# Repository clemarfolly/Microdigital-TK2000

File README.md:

# Microdigital - TK2000

A Microdigital Eletrônica Ltda foi uma das empresas pioneiras no mercado de microcomputadores no Brasil, tendo grande importância na popularização da informática durante a década de 1980. Fundada em 1979, a empresa se destacou por criar e distribuir uma série de microcomputadores compatíveis com modelos internacionais. A Microdigital se beneficiou da reserva de mercado imposta pelo governo brasileiro, o que levou a empresa a desenvolver produtos que atendessem à demanda interna por tecnologia, educação e entretenimento.

Entre os produtos está o TK2000, lançado oficialmente em 1984 após ser apresentado na Feira de Informática de 1983. Inspirado no Apple II, o TK2000 foi um microcomputador voltado para o mercado doméstico e educacional, parcialmente compatível com o software do Apple II, mas com algumas limitações em termos de hardware, o que o tornava mais acessível ao consumidor brasileiro. Equipado com uma CPU 6502, 16k de ROM e 64k de RAM, o TK2000 era, na verdade, um clone do Micro-Professor MPF-II, um modelo taiwanês fabricado pela Multitech (futura Acer). O sucesso do TK2000 consolidou a Microdigital como uma das líderes no mercado de microcomputadores no Brasil, contribuindo significativamente para a difusão da cultura computacional no país durante os anos 80. Em 1985, foi lançada uma versão aprimorada, o TK2000 II, que incluía uma opção de 128K de memória. O microcomputador foi descontinuado em 1987.

## Sobre essa reprodução

A reprodução do projeto foi realizada sem acesso físico à placa original, com base em fotos encontradas na internet. Para isso, utilizou-se os software Sprint Layout e o KiCad para desenhar o esquema e a placa de circuito impresso. A réplica ainda não foi produzida, e seu funcionamento não foi validado. Agradecemos às pessoas que disponibilizaram as fotos e o esquema original, permitindo que esse trabalho fosse possível.

 ### Datalhes da placa
A placa é dupla face e o tamanho final ficou com 237x170 mm.

### Comparação com a placa original
Embora eu não tenha tido acesso direto à placa original, me esforcei para que a recriação fosse a mais fiel possível. Algumas imagens de referência estavam em baixa resolução e precisaram ter suas proporções ajustadas, além de estarem com componentes e adesivos, o que dificultou a reprodução das trilhas que passavam por baixo deles.

A parte de RF foi removida e no lugar colocada uma saída de áudio. Além disso, o jumper que conecta o pino 28 da ROM U39 ao pino 7 do 74LS244 foi integrado diretamente ao roteamento da placa, permetindo o uso de uma ROM 27C128.

### Para confecção

Na seção de releases desta página, você encontrará todos os arquivos necessários para a fabricação da placa: o gerber em formato zip, o esquema em PDF e a lista interativa de materiais em HTML. Basta enviar o arquivo zip para a sua fabricante de PCB de preferência.

### Chip customizado

A montagem requer a gravação de um chip PLD GAL16V8, o conteúdo está na pasta PAL. Mais detalhes em: 

https://www.facebook.com/groups/cidadedosclassicos/posts/5769043533153302/?paipv=0&eav=AfbpHolPJ6P4nDAmXXkvS--qkC2yUR-xJ5SVl_j7wmNv-nLbxHa_C_v81FATnQMoCv0&_rdr

## Créditos

### Recriação da Placa: 

Clemar Folly Jr.

https://x.com/clemarfolly/ - https://www.facebook.com/clemarjr

### Fotos

Clube do TK90X

http://www.tk90x.com.br/Projetos_TK2000_clareamento.html

José Ferro - Recebido via E-mail

Tabajara Labs

http://tabalabs.com.br/tk2k/reparo_teclado/

Grupo Microdigital TK 2000 no Facebook

https://www.facebook.com/groups/2839171526116039/

Uma saída de som para o TK2000

https://www.victortrucco.com/TK/TK2000Som/TK2000Som

### Esquema

TK2000 - Esquema Elétrico Placa Principal - Datassette

https://datassette.org/manuais/hardware-tk-2000-microdigital-eletronica-manuais/tk2000-esquema-eletrico-placa-principal

#### Caso queira contribuir para que outras reproduções como esta sejam feitas, considere fazer uma doação.

Chave pix: clemarjr@gmail.com

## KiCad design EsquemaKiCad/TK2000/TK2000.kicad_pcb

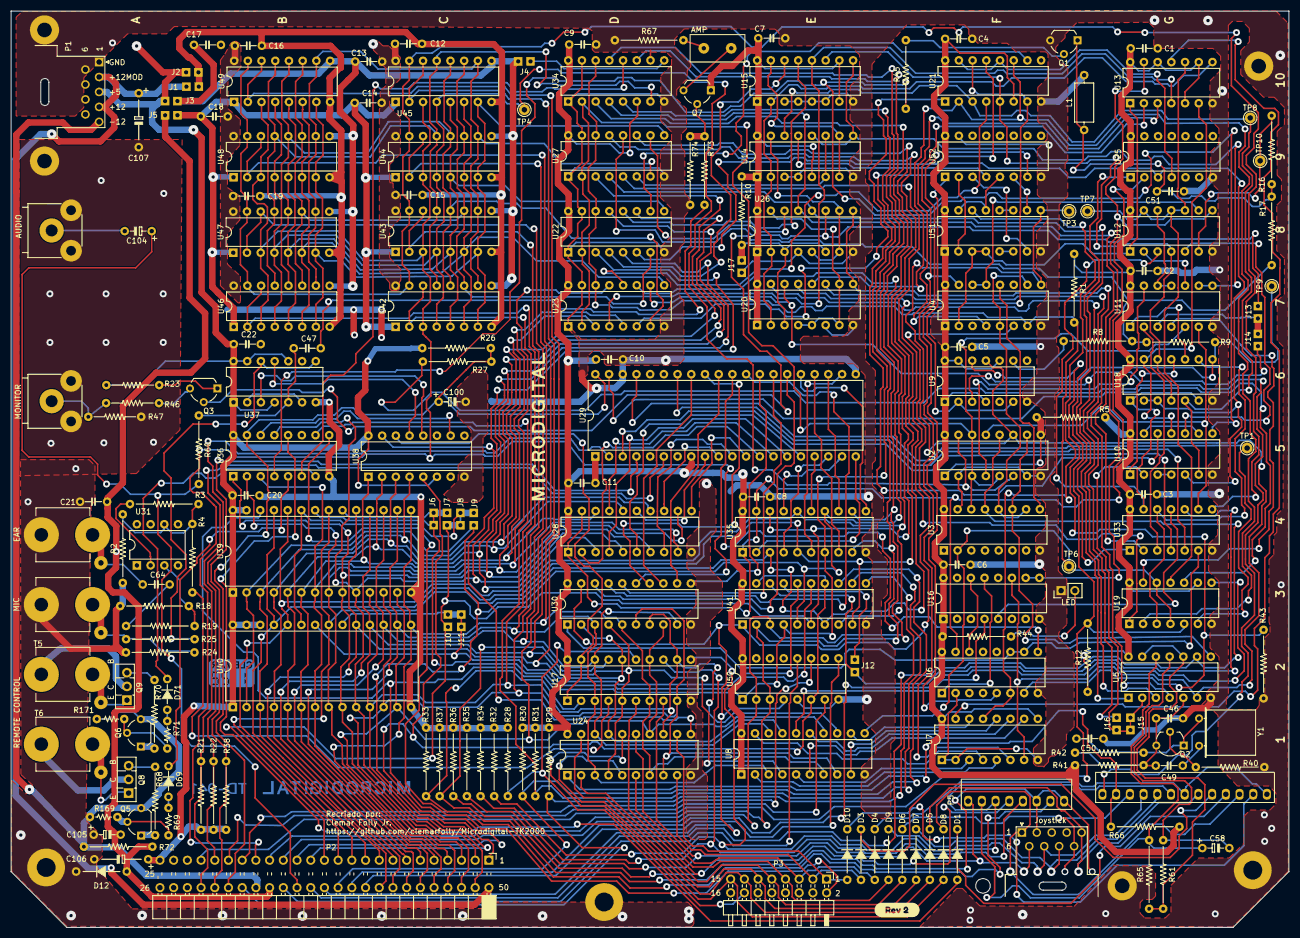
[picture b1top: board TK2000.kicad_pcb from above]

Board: 2 copper layers, 236.8 x 169.8 mm, 206 parts (0 on the bottom side), 255 nets.

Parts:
C1, C2, C3, C4, C5, C6, C7, C8, C9, C10, C11, C12, C13, C14, C15, C16, C17, C18, C19, C20, C21, C22: 0.1; C_Disc_D4.3mm_W1.9mm_P5.00mm
C46, C47, C49, C50, C51: C_Small; C_Disc_D4.3mm_W1.9mm_P5.00mm
C58, C100: C_Polarized_Small; C_Polarized_P5.00mm
C64: ?; C_Disc_D4.3mm_W1.9mm_P5.00mm
C104: 1uF; C_Polarized_P5.00mm
C105: 47uF; C_Polarized_P5.00mm
C106, C107: 100uF; C_Polarized_P10.00mm
D1, D3, D4, D5, D6, D7, D8, D9, D10: D_Small; Diodo_9.38mm
D12: 5V1; Diodo_9.38mm
D13: LED; PinHeader_1x02_P2.54mm_Vertical
D69, D71: 1N4148; Diodo_5.715mm
H1, H2, H3: MountingHole_Pad; MountingHole_3.5mm_Pad
H4, H6, H7, H8: MountingHole_Pad; MountingHole_2.7mm_Pad
H5: MountingHole_Pad; MountingHole_2.7mm
J1, J3, J4, J5, J7, J9, J10, J14, J16: SolderJumper_2_Open; Jumper_Open
J2: TK2000:Jumper_Open; Jumper_Open
J6, J8, J11, J12: SolderJumper_2_Open; Jumper_Bridged
J13, J15: Jumper_Bridged
J17: SolderJumper_2_Open_Small; Jumper_Open
J100: Joystick; DSUB-9_Male_Horizontal_P2.77x2.54mm_EdgePinOffset9.40mm
L1: 47uH; L_Axial_L7.0mm_D3.3mm_P10.16mm_Horizontal_Fastron_MICC
LS1: AMP; Connector_AMP
P1: POWER; DSUB-9_Male_Horizontal_P2.77x2.54mm_EdgePinOffset9.40mm
P2: Conector de Expansão; PinSocket_2x25_P2.54mm_Horizontal
P3: P3; PinHeader_2x08_P2.54mm_Horizontal
P5: Conector_P5; Connector_P5
Q1, Q3, Q5, Q6, Q7: BC548; TO-92_Wide
Q2: BF494B; TO-92_Wide_Invert
Q8, Q9: BD140; TO-126-3_Vertical
R1, R2, R5, R10, R12, R16, R21, R22, R26, R28, R29, R30, R31, R32, R33, R34, R35, R36, R37, R38, R43, R45, R61, R65, R66: 1k; Resistor_P12.7mm_Horizontal
R3: 1M; Resistor_P12.7mm_Horizontal
R4, R9, R18, R19, R25: 12k; Resistor_P12.7mm_Horizontal
R8, R27: 1k5; Resistor_P12.7mm_Horizontal
R17: 2k; Resistor_P12.7mm_Horizontal
R23, R46, R47: 1k; Resistor_P9.8mm_Horizontal
R24: 100; Resistor_P12.7mm_Horizontal
R40, R41, R42: 47; Resistor_P12.7mm_Horizontal
R44: 220; Resistor_P12.7mm_Horizontal
R60: 560; Resistor_P12.7mm_Horizontal
R67, R72, R73, R74: ?; Resistor_P12.7mm_Horizontal
R68, R70: 470; Resistor_P12.7mm_Horizontal
R69, R71: 5k6; Resistor_P5.08mm_Vertical
R169, R171: 3k3; Resistor_P5.08mm_Vertical
T2: MONITOR; RCA_AV-8,4-5A
T3: EAR; J2_Mono_Panel
T4: MIC; J2_Mono_Panel
T5: B - Remote; J2_Mono_Panel
T6: A - Remote; J2_Mono_Panel
T7: AUDIO; RCA_AV-8,4-5A
TP1, TP3, TP6, TP7, TP8, TP9, TP10: TestPoint_Small; Pin_D1.0mm_L10.0mm
TP4: ~{CAS}; Pin_D1.0mm_L10.0mm
U2, U16: 74LS194; DIP-16_W7.62mm
U3, U22, U23, U27, U34: 74LS153; DIP-16_W7.62mm
U4: 74LS175; DIP-16_W7.62mm
U5, U25: 74LS04; DIP-14_W7.62mm
U6: 74LS253; DIP-16_W7.62mm
U7: 74LS166; DIP-16_W7.62mm
U8, U24: 74LS273; DIP-20_W7.62mm
U9, U37: 74LS74; DIP-14_W7.62mm
U10, U11: 74LS02; DIP-14_W7.62mm
U12: 74LS11; DIP-14_W7.62mm
U13: 74LS86; DIP-14_W7.62mm
U14, U15, U20, U26: 74LS161; DIP-16_W7.62mm
U17, U28, U35: 74LS244; DIP-20_W7.62mm
U18: 74LS51; DIP-14_W7.62mm
U19: 74LS08; DIP-14_W7.62mm
U21: 74LS283; DIP-16_W7.62mm
U29: 6502; DIP-40_W15.24mm
U30: 74LS245; DIP-20_W7.62mm
U31: LM741; DIP-8_W7.62mm
U33: 74LS32; DIP-14_W7.62mm
U36: 74LS259; DIP-16_W7.62mm
U38, U50: 74LS138; DIP-16_W7.62mm
U39, U40: 2764; DIP-28_W15.24mm
U41: PAL14L4; DIP-20_W7.62mm
U42: 4116_U42; DIP-16_W7.62mm
U43: 4116_U43; DIP-16_W7.62mm
U44, U45, U46, U47: 4116_U47; DIP-16_W7.62mm
U48, U49: 4116; DIP-16_W7.62mm
U51: 74LS174; DIP-16_W7.62mm
U52: 74LS157; DIP-16_W7.62mm
Y1: Crystal; Crystal_HC52-U_Horizontal
kibuzzard-6AD42836: G***; kibuzzard-6AD42836

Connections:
+5V: C1.1, C2.1, C3.1, C4.1, C5.1, C6.1, C7.1, C8.1, C9.1, C10.1, C11.1, C20.1, C22.1, C106.1, J2.2 (B), J3.2 (B), P1.3, P2.25, Q7.1 (C), R1.1, R5.2, R10.1, R12.1, R21.1, R22.1, R23.2, R26.1, R29.1, R30.1, R31.1, R38.1, R41.1, R44.2, R66.1, U2.16 (VCC), U3.16 (VCC), U4.1 (~Mr), U4.16 (VCC), U5.14 (VCC), U6.16 (VCC), U7.9 (~Clr), U7.16 (VCC), U8.1 (~MR), U8.20 (VCC), U9.1 (CL1), U9.4 (PR1), U9.10 (PR2), U9.13 (CL2), U9.14 (VCC), U10.14 (VCC), U11.14 (VCC), U12.14 (VCC), U13.5, U13.9, U13.12, U13.14 (VCC), U14.1 (~MR), U14.5 (D2), U14.16 (VCC), U15.1 (~MR), U15.7 (CEP), U15.10 (CET), U15.16 (VCC), U16.1 (Mr), U16.16 (VCC), U17.20 (VCC), U18.14 (VCC), U19.9, U19.14 (VCC), U20.1 (~MR), U20.16 (VCC), U21.6 (B1), U21.16 (VCC), U22.16 (VCC), U23.16 (VCC), U24.20 (VCC), U25.14 (VCC), U26.1 (~MR), U26.16 (VCC), U27.16 (VCC), U28.20 (VCC), U29.8 (VCC), U30.20 (VCC), U31.7 (V+), U33.14 (VCC), U34.6 (I0a), U34.16 (VCC), U35.20 (VCC), U36.16 (VCC), U37.1 (CL1), U37.4 (PR1), U37.10 (PR2), U37.13 (CL2), U37.14 (VCC), U38.6 (G1), U38.16 (VDD), U39.1 (VPP), U39.27 (~PGM), U39.28 (VCC), U40.1 (VPP), U40.26 (NC), U40.27 (~PGM), U40.28 (VCC), U41.20 (VCC), U50.16 (VDD), U51.1 (~Mr), U51.16 (VCC), U52.16 (VCC)
+12V: C107.1, J1.2 (B), P1.2, P1.4, P2.50
-5V: C21.1, C105.2, D12.2 (A), J5.2 (B), P2.34, R72.1, U31.4 (V-)
-12V: P1.5, P2.33, Q5.3 (E), Q6.3 (E), R72.2, R169.1, R171.2
GND: C1.2, C2.2, C3.2, C4.2, C5.2, C6.2, C7.2, C8.2, C9.2, C10.2, C11.2, C12.2, C13.2, C14.2, C15.2, C16.2, C17.2, C18.2, C19.2, C20.2, C21.2, C22.2, C46.2, C50.1, C51.2, C100.2, C105.1, C106.2, C107.2, D12.1 (K), D13.1 (K), H1.1, H2.1, H3.1, H4.1, H6.1, H7.1, H8.1, J17.1 (A), L1.2, P1.1, P1.6, P1.7, P1.8, P1.9, P2.26, P3.4, P3.6, P3.8, P3.10, P3.12, Q1.3 (E), R2.1, R18.1, R24.1, R28.1, R32.1, R33.1, R34.1, R35.1, R36.1, R37.1, R40.1, R43.2, R47.1, R67.1, R74.1, T2.2 (Ext), T3.2 (Ext), T4.2 (Ext), T7.2 (Ext), U2.2 (Dsr), U2.7 (Dsl), U2.8 (GND), U3.8 (GND), U3.15 (~Eb), U4.8 (GND), U5.7 (GND), U6.2 (A1), U6.8 (GND), U7.1 (Ds), U7.2 (D0), U7.8 (GND), U8.10 (GND), U9.7 (GND), U10.7 (GND), U11.7 (GND), U12.7 (GND), U13.7 (GND), U14.3 (D0), U14.4 (D1), U14.8 (GND), U15.3 (D0), U15.4 (D1), U15.5 (D2), U15.6 (D3), U15.8 (GND), U16.8 (GND), U17.10 (GND), U18.7 (GND), U19.7 (GND), U20.6 (D3), U20.8 (GND), U21.8 (GND), U22.1 (~Ea), U22.8 (GND), U22.15 (~Eb), U23.1 (~Ea), U23.8 (GND), U23.15 (~Eb), U24.10 (GND), U25.7 (GND), U26.4 (D1), U26.8 (GND), U27.1 (~Ea), U27.8 (GND), U27.15 (~Eb), U28.10 (GND), U29.1 (VSS), U29.21 (VSS), U29.38 (SO), U30.10 (GND), U33.7 (GND), U34.1 (~Ea), U34.8 (GND), U34.10 (I0b), U34.15 (~Eb), U35.10 (GND), U36.8 (GND), U37.7 (GND), U38.8 (VSS), U39.14 (GND), U40.14 (GND), U41.10 (VSS), U42.16 (GND), U43.16, U44.16, U45.16, U46.16, U47.16, U48.16, U49.16, U50.5 (~G2B), U50.8 (VSS), U51.8 (GND), U52.8 (GND), U52.15 (~E)
J3_P1: C13.1, C17.1, J3.1 (A), J4.1 (A), U42.9, U43.9, U44.9, U45.9, U46.9, U47.9, U48.9, U49.9
unnamed: C47.2, R73.1
unnamed: C49.1, Y1.1
unnamed: C58.1, P5.2, R65.2, U5.12
unnamed: C58.2, R61.1, U5.11
unnamed: C64.2, R19.2
unnamed: D1.2 (A), U36.12 (Q7)
unnamed: D1.1 (K), P5.18
unnamed: D3.2 (A), P3.3, U24.9 (4Q)
unnamed: D3.1 (K), P5.17
unnamed: D4.2 (A), P3.5, U24.15 (6Q)
unnamed: D4.1 (K), P5.15, P5.21
unnamed: D5.2 (A), P3.13, U24.5 (2Q)
unnamed: D5.1 (K), J100.5, P5.16
unnamed: D6.2 (A), P3.9, U24.2 (1Q)
unnamed: D6.1 (K), J100.9, P5.11
unnamed: D7.2 (A), P3.11, U24.19 (8Q)
unnamed: D7.1 (K), J100.8, P5.13
unnamed: D8.2 (A), P3.15, U24.16 (7Q)
unnamed: D8.1 (K), J100.1, P5.19
unnamed: D9.2 (A), P3.7, U24.6 (3Q)
unnamed: D9.1 (K), J100.7, P5.12
unnamed: D10.2 (A), P3.1, U24.12 (5Q)
unnamed: D10.1 (K), P5.20
unnamed: D13.2 (A), R44.1
unnamed: D69.2 (A), R69.1
unnamed: D69.1 (K), U36.5 (Q1)
unnamed: D71.2 (A), R71.1
unnamed: D71.1 (K), U36.7 (Q3)
unnamed: J4.2 (B), U34.9 (Zb)
unnamed: J6.1 (A), J6.2 (B), J7.1 (A), U39.20 (~CE), U39.22 (~OE), U41.15
unnamed: J10.1 (A), J11.1 (A), J11.2 (B), U40.20 (~CE), U40.22 (~OE), U41.16
unnamed: J12.1 (A), U41.17
unnamed: J12.2 (B), U33.10, U41.18
unnamed: J13.1 (A), J14.2 (B), U11.3
unnamed: J13.2 (B), U26.11 (Q3), U27.12 (I2b)
unnamed: J14.1 (A), U5.1, U20.14 (Q0), U23.10 (I0b)
unnamed: J15.1 (A), J15.2 (B), J16.2 (B), U5.2, U10.2
unnamed: J16.1 (A), U20.11 (Q3)
unnamed: J17.2 (B), R10.2, U20.3 (D0), U26.3 (D0), U26.6 (D3)
unnamed: LS1.2, R67.2
unnamed: P5.22, R27.2
unnamed: Q1.2 (B), R45.2
unnamed: C51.1, L1.1, Q1.1 (C), R16.2, R17.1
unnamed: C50.2, Q2.1 (B), R42.2, Y1.2
unnamed: C46.1, C49.2, Q2.3 (C), R41.2, R42.1, U5.5
unnamed: Q2.2 (E), R40.2
unnamed: Q3.2 (B), R8.2, R9.2, R17.2
unnamed: Q3.1 (C), R23.1
unnamed: Q3.3 (E), R46.2
unnamed: Q5.2 (B), R69.2, R169.2
unnamed: Q5.1 (C), R68.2
unnamed: Q6.2 (B), R71.2, R171.1
unnamed: Q6.1 (C), R70.1
unnamed: Q7.2 (B), R73.2, R74.2
unnamed: LS1.1, Q7.3 (E)
unnamed: Q8.3 (B), R68.1
unnamed: Q8.2 (C), T6.2 (Ext)
unnamed: Q8.1 (E), T6.1 (In)
unnamed: Q9.3 (B), R70.2
unnamed: Q9.2 (C), T5.2 (Ext)
unnamed: Q9.1 (E), T5.1 (In)
unnamed: R2.2, R3.2, R4.1, U31.6
unnamed: R16.1, TP10.1, U12.6
unnamed: R61.2, R65.1, U5.10, U5.13
unnamed: R46.1, R47.2, T2.1 (In)
unnamed: C64.1, T3.1 (In)
unnamed: R24.2, R25.2, T4.1 (In)
unnamed: C104.2, T7.1 (In)
unnamed: TP7.1, U12.10, U12.11, U12.13, U13.10, U19.11
unnamed: R5.1, U2.1 (Mr), U2.9 (S0)
unnamed: U2.3 (P0), U2.5 (P2), U2.14 (Q1), U3.14 (S0), U11.5, U22.2 (S1), U23.2 (S1), U27.2 (S1), U34.2 (S1)
unnamed: U2.4 (P1), U11.13
unnamed: TP4.1, U2.6 (P3), U2.15 (Q0), U42.4, U43.4, U44.4, U45.4, U46.4, U47.4, U48.4, U49.4
unnamed: U2.13 (Q2), U11.6, U33.9
unnamed: U2.10 (S1), U3.11 (I1b), U5.8
unnamed: U3.10 (I0b), U3.12 (I2b), U4.5 (D1), U4.10 (Q2)
unnamed: U3.9 (Zb), U4.12 (D2)
unnamed: U4.4 (D0), U13.3
unnamed: U4.13 (D3), U4.14 (~Q3), U12.9
unnamed: U4.2 (Q0), U12.1, U13.1, U51.3 (D0), U51.4 (D1)
unnamed: U4.15 (Q3), U7.6 (CE), U13.2
unnamed: R43.1, U6.7 (Za), U9.12 (D2)
unnamed: U7.3 (D1), U8.5 (2Q)
unnamed: U7.4 (D2), U8.19 (8Q)
unnamed: U7.5 (D3), U8.2 (1Q)
unnamed: U7.10 (D4), U8.6 (3Q)
unnamed: U7.11 (D5), U8.15 (6Q)
unnamed: U7.12 (D6), U8.9 (4Q)
unnamed: U7.14 (D7), U8.12 (5Q)
unnamed: U7.15 (PE), U13.11
unnamed: R9.1, TP9.1, U9.3 (CK1), U18.8
unnamed: R8.1, U9.9 (Q2)
unnamed: U10.1, U18.11
unnamed: U10.3, U10.4
unnamed: U10.10, U12.5
unnamed: U10.11, U13.6, U18.13
unnamed: U10.9, U10.13
unnamed: U11.1, U18.10
unnamed: U11.2, U33.3
unnamed: U11.4, U19.13
unnamed: U11.10, U12.2
unnamed: U11.11, U11.12, U12.12
unnamed: U12.3, U18.1, U18.6, U33.13
unnamed: U14.7 (CEP), U14.10 (CET), U15.15 (TC)
unnamed: U13.8, U14.2 (CP), U15.2 (CP), U20.2 (CP), U26.2 (CP)
unnamed: U14.6 (D3), U14.11 (Q3), U27.6 (I0a)
unnamed: TP8.1, U10.6, U14.14 (Q0), U18.5, U21.3 (A2)
unnamed: U10.5, U14.13 (Q1), U18.2, U18.3, U25.3
unnamed: U11.8, U11.9, U14.9 (~PE), U14.12 (Q2), U15.9 (~PE)
unnamed: U14.15 (TC), U26.5 (D2), U26.7 (CEP), U26.10 (CET)
unnamed: U15.14 (Q0), U22.4 (I2a)
unnamed: U15.13 (Q1), U22.12 (I2b)
unnamed: U13.4, U15.12 (Q2), U23.4 (I2a)
unnamed: U12.4, U15.11 (Q3), U18.4, U18.12, U21.5 (A1)
unnamed: TP3.1, U2.11 (Cp), U4.9 (Cp), U5.6, U7.7 (Clk), U9.11 (CK2), U16.11 (Cp), U51.9 (Cp)
unnamed: U8.16 (7Q), U16.4 (P1)
unnamed: U16.5 (P2), U33.11
unnamed: U6.14 (A0), U16.14 (Q1)
unnamed: U6.1 (~OEa), U16.13 (Q2)
unnamed: U12.8, U13.13, U16.9 (S0), U16.10 (S1)
unnamed: P5.7, R33.2, U17.2 (I0a)
unnamed: P5.3, P5.14, R32.2, U17.11 (I0b)
unnamed: R4.2, U17.4 (I1a)
unnamed: P5.5, R34.2, U17.13 (I1b)
unnamed: P5.4, R36.2, U17.6 (I2a)
unnamed: P3.14, R28.2, U17.15 (I2b)
unnamed: J100.6, P5.1, R35.2, U17.8 (I3a)
unnamed: J100.2, P5.6, P5.8, R37.2, U17.17 (I3b)
unnamed: U17.1 (~OEa), U17.19 (~OEb), U38.14 (Y1)
unnamed: U18.9, U19.3, U33.12
unnamed: U20.4 (D1), U20.5 (D2), U20.7 (CEP), U20.10 (CET), U26.15 (TC)
unnamed: U19.1, U20.13 (Q1), U21.7 (C0), U21.14 (A3)
unnamed: U19.2, U20.12 (Q2), U21.2 (B2), U21.11 (B4)
unnamed: U5.3, U20.15 (TC)
unnamed: U5.4, U20.9 (~PE), U26.9 (~PE)
unnamed: U21.12 (A4), U21.15 (B3), U25.4
unnamed: U21.4 (S1), U23.12 (I2b)
unnamed: U21.1 (S2), U23.6 (I0a)
unnamed: U21.13 (S3), U22.6 (I0a)
unnamed: U21.10 (S4), U22.10 (I0b)
unnamed: R1.2, TP6.1, U3.2 (S1), U4.7 (Q1), U8.11 (CP), U19.4, U19.12, U22.14 (S0), U23.14 (S0), U27.14 (S0), U34.14 (S0)
unnamed: U22.7 (Za), U42.11, U43.11, U44.11, U45.11, U46.11, U47.11, U48.11, U49.11
unnamed: U22.9 (Zb), U42.5, U43.5, U44.5, U45.5, U46.5, U47.5, U48.5, U49.5
unnamed: U23.7 (Za), U42.12, U43.12, U44.12, U45.12, U46.12, U47.12, U48.12, U49.12
unnamed: U23.9 (Zb), U42.6, U43.6, U44.6, U45.6, U46.6, U47.6, U48.6, U49.6
unnamed: U24.11 (CP), U38.15 (Y0)
unnamed: P5.10, R66.2, U24.1 (~MR)
unnamed: U26.14 (Q0), U27.10 (I0b)
unnamed: U26.13 (Q1), U33.2, U34.4 (I2a)
unnamed: U26.12 (Q2), U27.4 (I2a), U33.1
unnamed: U27.7 (Za), U42.10, U43.10, U44.10, U45.10, U46.10, U47.10, U48.10, U49.10
unnamed: U27.9 (Zb), U42.7, U43.7, U44.7, U45.7, U46.7, U47.7, U48.7, U49.7
unnamed: U28.2 (I0a), U29.13 (AB4)
unnamed: U28.11 (I0b), U29.12 (AB3)
unnamed: U28.4 (I1a), U29.15 (AB6)
unnamed: U28.13 (I1b), U29.10 (AB1)
unnamed: U28.6 (I2a), U29.16 (AB7)
unnamed: U28.15 (I2b), U29.9 (AB0)
unnamed: U28.8 (I3a), U29.11 (AB2)
unnamed: U28.17 (I3b), U29.14 (AB5)
unnamed: U6.15 (~OEb), U25.2, U28.1 (~OEa), U28.19 (~OEb), U35.1 (~OEa), U35.19 (~OEb)
unnamed: U29.17 (AB8), U35.15 (I2b)
unnamed: U29.18 (AB9), U35.4 (I1a)
unnamed: U29.19 (AB10), U35.17 (I3b)
unnamed: U29.20 (AB11), U35.2 (I0a)
unnamed: U29.22 (AB12), U35.6 (I2a)
unnamed: U29.23 (AB13), U35.13 (I1b)
unnamed: U29.24 (AB14), U35.8 (I3a)
unnamed: U29.25 (AB15), U35.11 (I0b)
unnamed: U29.33 (DB0), U30.13 (B6)
unnamed: U29.32 (DB1), U30.14 (B5)
unnamed: U29.31 (DB2), U30.12 (B7)
unnamed: U29.30 (DB3), U30.15 (B4)
unnamed: U29.29 (DB4), U30.17 (B2)
unnamed: U29.28 (DB5), U30.11 (B8)
unnamed: U29.27 (DB6), U30.16 (B3)
unnamed: U29.26 (DB7), U30.18 (B1)
unnamed: TP1.1, U19.6, U29.37 (PHI0)
unnamed: U29.3 (PHI1), U33.4
unnamed: U19.10, U29.39 (PHI2)
unnamed: U29.34 (R/~W), U33.5
unnamed: U6.10 (I0b), U6.11 (I1b), U30.1 (DIR), U33.6
unnamed: R18.2, R19.1, U31.3 (+)
unnamed: R3.1, U31.2 (-)
unnamed: U34.12 (I2b), U36.6 (Q2)
unnamed: U34.7 (Za), U42.13, U43.13, U44.13, U45.13, U46.13, U47.13, U48.13, U49.13
unnamed: R45.1, U10.8, U36.4 (Q0)
unnamed: P3.2, U36.9 (Q4)
unnamed: R31.2, U36.10 (Q5), U41.12
unnamed: U36.14 (~E), U38.10 (Y5)
unnamed: U37.3 (CK1), U38.12 (Y3)
unnamed: U37.11 (CK2), U38.13 (Y2)
unnamed: U37.2 (D1), U37.6 (~Q1)
unnamed: R25.1, U37.8 (~Q2), U37.12 (D2)
unnamed: C47.1, R60.1, U37.5 (Q1)
unnamed: U33.8, U42.15, U43.15, U44.15, U45.15, U46.15, U47.15, U48.15, U49.15
unnamed: U51.5 (Q1), U51.6 (D2)
unnamed: U51.11 (D3), U51.12 (Q4)
unnamed: U51.13 (D4), U51.15 (Q5), U52.5 (I0b)
unnamed: U6.6 (I0a), U7.13 (Qh), U51.14 (D5)
unnamed: U51.2 (Q0), U52.2 (I0a)
unnamed: U51.7 (Q2), U52.3 (I1a)
unnamed: U51.10 (Q3), U52.6 (I1b)
unnamed: U9.2 (D1), U9.6 (~Q1), U52.1 (S)
unnamed: U10.12, U52.4 (Za)
unnamed: U6.5 (I1a), U52.7 (Zb)
P2_2M: P2.37, U2.12 (Q3), U3.13 (I3b), U5.9
P2_A0: P2.2, U22.3 (I3a), U28.5 (O2b), U36.13 (D), U39.10 (A0), U40.10 (A0)
P2_A1: P2.3, U22.13 (I3b), U28.7 (O1b), U36.1 (A0), U39.9 (A1), U40.9 (A1)
P2_A2: P2.4, U23.3 (I3a), U28.12 (O3a), U36.2 (A1), U39.8 (A2), U40.8 (A2)
P2_A3: P2.5, U23.13 (I3b), U28.9 (O0b), U36.3 (A2), U39.7 (A3), U40.7 (A3)
P2_A4: P2.6, U23.5 (I1a), U28.18 (O0a), U38.1 (A), U39.6 (A4), U40.6 (A4)
P2_A5: P2.7, U22.5 (I1a), U28.3 (O3b), U38.2 (B), U39.5 (A5), U40.5 (A5)
P2_A6: P2.8, U22.11 (I1b), U28.16 (O1a), U38.3 (C), U39.4 (A6), U40.4 (A6)
P2_A7: P2.9, U27.3 (I3a), U28.14 (O2a), U38.4 (~G2A), U39.3 (A7), U40.3 (A7)
P2_A8: P2.10, U27.13 (I3b), U35.5 (O2b), U39.25 (A8), U40.25 (A8), U41.9
P2_A9: P2.11, U23.11 (I1b), U35.16 (O1a), U39.24 (A9), U40.24 (A9), U41.8
P2_A10: P2.12, U27.5 (I1a), U35.3 (O3b), U39.21 (A10), U40.21 (A10), U41.7
P2_A11: J7.2 (B), J8.1 (A), J8.2 (B), J9.2 (B), J10.2 (B), P2.13, U27.11 (I1b), U35.18 (O0a), U39.23 (A11), U40.23 (A11), U41.6
P2_A12: J9.1 (A), P2.14, U34.3 (I3a), U35.14 (O2a), U39.2 (A12), U40.2 (A12), U41.5
P2_A13: P2.15, U34.5 (I1a), U35.7 (O1b), U39.26 (A13), U41.4, U50.1 (A)
P2_A14: P2.16, U34.11 (I1b), U35.12 (O3a), U41.3, U50.2 (B)
P2_A15: P2.17, U34.13 (I3b), U35.9 (O0b), U41.2, U50.3 (C)
P2_D0: P2.49, U8.13 (5D), U17.12 (O3a), U24.13 (5D), U30.7 (A6), U39.11 (D0), U40.11 (D0), U42.2 (DI), U42.14 (DO)
P2_D1: P2.48, U8.8 (4D), U17.9 (O0b), U24.8 (4D), U30.6 (A5), U39.12 (D1), U40.12 (D1), U43.2 (DI), U43.14 (DO)
P2_D2: P2.47, U8.14 (6D), U17.14 (O2a), U24.14 (6D), U30.8 (A7), U39.13 (D2), U40.13 (D2), U44.2 (DI), U44.14 (DO)
P2_D3: P2.46, U8.7 (3D), U17.7 (O1b), U24.7 (3D), U30.5 (A4), U39.15 (D3), U40.15 (D3), U45.2 (DI), U45.14 (DO)
P2_D4: P2.45, U8.3 (1D), U17.3 (O3b), U24.3 (1D), U30.3 (A2), U39.16 (D4), U40.16 (D4), U46.2 (DI), U46.14 (DO)
P2_D5: P2.44, U8.18 (8D), U17.18 (O0a), U24.18 (8D), U30.9 (A8), U39.17 (D5), U40.17 (D5), U47.2 (DI), U47.14 (DO)
P2_D6: P2.43, U8.4 (2D), U17.5 (O2b), U24.4 (2D), U30.4 (A3), U39.18 (D6), U40.18 (D6), U48.2 (DI), U48.14 (DO)
P2_D7: P2.42, U8.17 (7D), U17.16 (O1a), U24.17 (7D), U30.2 (A1), U39.19 (D7), U40.19 (D7), U49.2 (DI), U49.14 (DO)
P2_DMA: P2.22, R12.2, U19.5, U25.1
P2_EXT6: P2.35, U50.12 (Y3)
P2_EXT8: P2.19, U50.11 (Y4)
P2_EXTC: P2.41, U50.9 (Y6)
P2_EXTE: P2.20, U50.7 (Y7)
P2_EXTM: P2.32, R29.2, U41.11
P2_IODIS: P2.39, R30.2, U41.13
P2_IOSEL: P2.1, U38.5 (~G2B), U41.14, U41.19, U50.6 (G1)
P2_IRQ: P2.30, R38.2, U29.4 (~IRQ)
P2_NMI: P2.29, R21.2, U29.6 (~NMI)
P2_PHI1: P2.38, U4.6 (~Q1), U30.19 (~CE), U41.1, U50.4 (~G2A)
P2_PHI2: P2.40, U19.8
P2_RDY: P2.21, R22.2, U29.2 (RDY)
P2_RESET: C100.1, P2.31, R26.2, R27.1, U29.40 (~RES), U36.15 (~Clr)
P2_R~W: P2.18, U6.9 (Zb), U42.3, U43.3, U44.3, U45.3, U46.3, U47.3, U48.3, U49.3
P2_SOUND: C104.1, P2.36, R60.2
Vnm: C14.1, C18.1, J5.1 (A), U42.1, U43.1, U44.1, U45.1, U46.1, U47.1, U48.1, U49.1
Vpm: C12.1, C15.1, C16.1, C19.1, J1.1 (A), J2.1 (A), U42.8, U43.8, U44.8, U45.8, U46.8, U47.8, U48.8, U49.8

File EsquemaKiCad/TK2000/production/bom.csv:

Designator,Footprint,Quantity,Value,LCSC Part #
"C1, C10, C11, C12, C13, C14, C15, C16, C17, C18, C19, C2, C20, C21, C22, C3, C4, C5, C6, C7, C8, C9",C_Disc_D4.3mm_W1.9mm_P5.00mm,22,0.1,
"C100, C58",C_Polarized_P5.00mm,2,C_Polarized_Small,
C104,C_Polarized_P5.00mm,1,1uF,
C105,C_Polarized_P5.00mm,1,47uF,
"C106, C107",C_Polarized_P10.00mm,2,100uF,
"C46, C47, C49, C50, C51",C_Disc_D4.3mm_W1.9mm_P5.00mm,5,C_Small,
C64,C_Disc_D4.3mm_W1.9mm_P5.00mm,1,?,
"D1, D10, D3, D4, D5, D6, D7, D8, D9",Diodo_9.38mm,9,D_Small,
D12,Diodo_9.38mm,1,5V1,
D13,PinHeader_1x02_P2.54mm_Vertical,1,LED,
"D69, D71",Diodo_5.715mm,2,1N4148,
"H1, H2, H3",MountingHole_3.5mm_Pad,3,MountingHole_Pad,
"H4, H6, H7, H8",MountingHole_2.7mm_Pad,4,MountingHole_Pad,
H5,MountingHole_2.7mm,1,MountingHole_Pad,
"J1, J10, J14, J16, J3, J4, J5, J7, J9",Jumper_Open,9,SolderJumper_2_Open,
J100,DSUB-9_Male_Horizontal_P2.77x2.54mm_EdgePinOffset9.40mm,1,Joystick,
"J11, J12, J6, J8",Jumper_Bridged,4,SolderJumper_2_Open,
"J13, J15",Jumper_Bridged,2,~,
J17,Jumper_Open,1,SolderJumper_2_Open_Small,
J2,Jumper_Open,1,TK2000:Jumper_Open,
L1,L_Axial_L7.0mm_D3.3mm_P10.16mm_Horizontal_Fastron_MICC,1,47uH,
LS1,Connector_AMP,1,AMP,
P1,DSUB-9_Male_Horizontal_P2.77x2.54mm_EdgePinOffset9.40mm,1,POWER,
P2,PinSocket_2x25_P2.54mm_Horizontal,1,Conector de Expansão,
P3,PinHeader_2x08_P2.54mm_Horizontal,1,P3,
P5,Connector_P5,1,Conector_P5,
"Q1, Q3, Q5, Q6, Q7",TO-92_Wide,5,BC548,
Q2,TO-92_Wide_Invert,1,BF494B,
"Q8, Q9",TO-126-3_Vertical,2,BD140,
"R1, R10, R12, R16, R2, R21, R22, R26, R28, R29, R30, R31, R32, R33, R34, R35, R36, R37, R38, R43, R45, R5, R61, R65, R66",Resistor_P12.7mm_Horizontal,25,1k,
"R169, R171",Resistor_P5.08mm_Vertical,2,3k3,
R17,Resistor_P12.7mm_Horizontal,1,2k,
"R18, R19, R25, R4, R9",Resistor_P12.7mm_Horizontal,5,12k,
"R23, R46, R47",Resistor_P9.8mm_Horizontal,3,1k,
R24,Resistor_P12.7mm_Horizontal,1,100,
"R27, R8",Resistor_P12.7mm_Horizontal,2,1k5,
R3,Resistor_P12.7mm_Horizontal,1,1M,
"R40, R41, R42",Resistor_P12.7mm_Horizontal,3,47,
R44,Resistor_P12.7mm_Horizontal,1,220,
R60,Resistor_P12.7mm_Horizontal,1,560,
"R67, R72, R73, R74",Resistor_P12.7mm_Horizontal,4,?,
"R68, R70",Resistor_P12.7mm_Horizontal,2,470,
"R69, R71",Resistor_P5.08mm_Vertical,2,5k6,
T2,"RCA_AV-8,4-5A",1,MONITOR,
T3,J2_Mono_Panel,1,EAR,
T4,J2_Mono_Panel,1,MIC,
T5,J2_Mono_Panel,1,B - Remote,
T6,J2_Mono_Panel,1,A - Remote,
T7,"RCA_AV-8,4-5A",1,AUDIO,
"TP1, TP10, TP3, TP6, TP7, TP8, TP9",Pin_D1.0mm_L10.0mm,7,TestPoint_Small,
TP4,Pin_D1.0mm_L10.0mm,1,~{CAS},
"U10, U11",DIP-14_W7.62mm,2,74LS02,
U12,DIP-14_W7.62mm,1,74LS11,
U13,DIP-14_W7.62mm,1,74LS86,
"U14, U15, U20, U26",DIP-16_W7.62mm,4,74LS161,
"U16, U2",DIP-16_W7.62mm,2,74LS194,
"U17, U28, U35",DIP-20_W7.62mm,3,74LS244,
U18,DIP-14_W7.62mm,1,74LS51,
U19,DIP-14_W7.62mm,1,74LS08,
U21,DIP-16_W7.62mm,1,74LS283,
"U22, U23, U27, U3, U34",DIP-16_W7.62mm,5,74LS153,
"U24, U8",DIP-20_W7.62mm,2,74LS273,
"U25, U5",DIP-14_W7.62mm,2,74LS04,
U29,DIP-40_W15.24mm,1,6502,
U30,DIP-20_W7.62mm,1,74LS245,
U31,DIP-8_W7.62mm,1,LM741,
U33,DIP-14_W7.62mm,1,74LS32,
U36,DIP-16_W7.62mm,1,74LS259,
"U37, U9",DIP-14_W7.62mm,2,74LS74,
"U38, U50",DIP-16_W7.62mm,2,74LS138,
"U39, U40",DIP-28_W15.24mm,2,2764,
U4,DIP-16_W7.62mm,1,74LS175,
U41,DIP-20_W7.62mm,1,PAL14L4,
U42,DIP-16_W7.62mm,1,4116_U42,
U43,DIP-16_W7.62mm,1,4116_U43,
"U44, U45, U46, U47",DIP-16_W7.62mm,4,4116_U47,
"U48, U49",DIP-16_W7.62mm,2,4116,
U51,DIP-16_W7.62mm,1,74LS174,
U52,DIP-16_W7.62mm,1,74LS157,
U6,DIP-16_W7.62mm,1,74LS253,
U7,DIP-16_W7.62mm,1,74LS166,
Y1,Crystal_HC52-U_Horizontal,1,Crystal,

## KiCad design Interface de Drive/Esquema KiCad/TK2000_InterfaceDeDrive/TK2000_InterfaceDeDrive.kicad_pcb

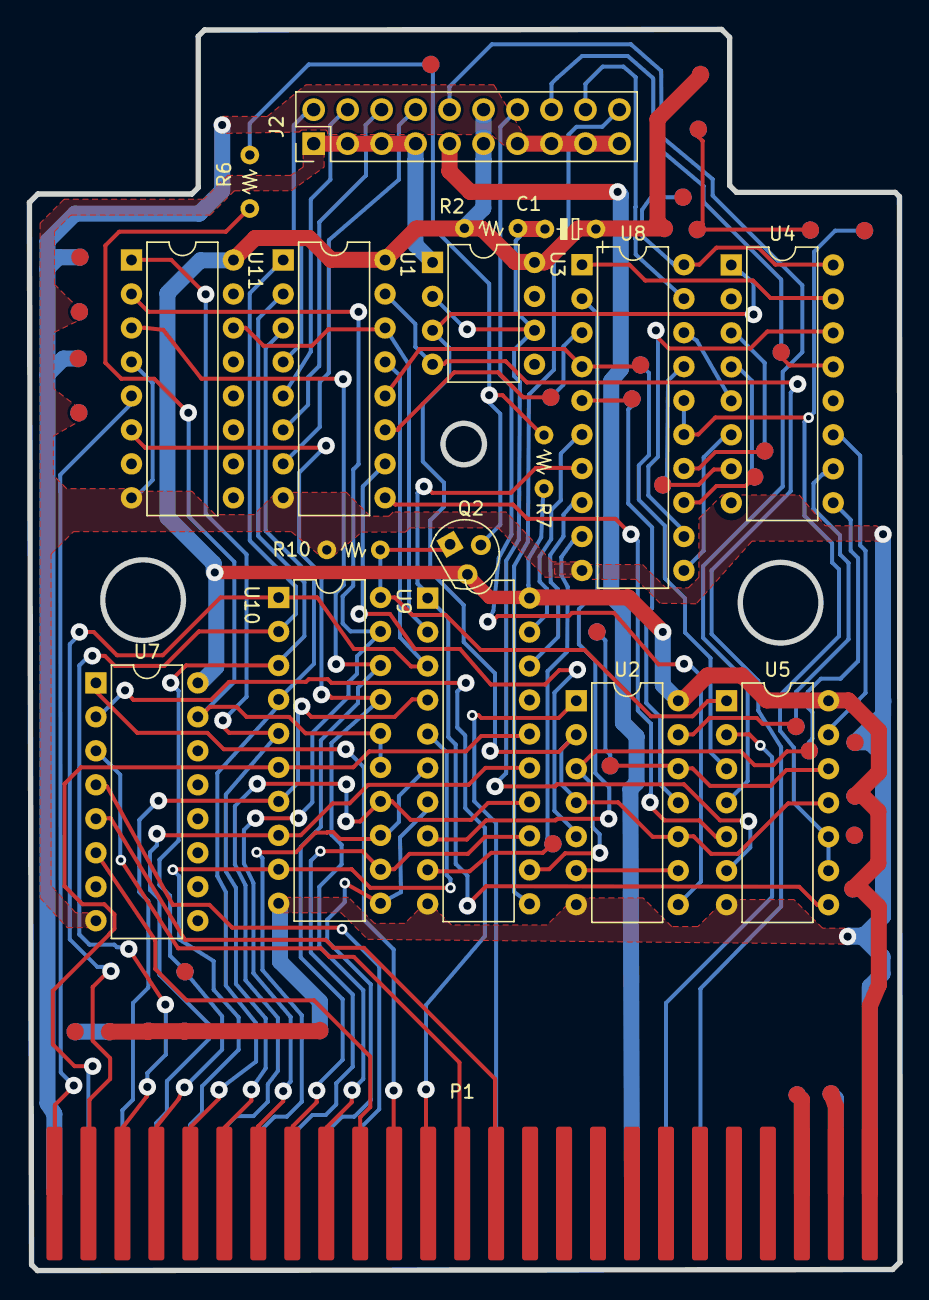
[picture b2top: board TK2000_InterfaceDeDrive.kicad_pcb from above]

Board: 2 copper layers, 65.1 x 92.8 mm, 18 parts (0 on the bottom side), 51 nets.

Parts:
C1: 10uF; C_Polarized_P5.00mm
J2: CN (DISK DRIVE); PinSocket_2x10_P2.54mm_Vertical
P1: Conector de Expansão; Conector Edge
Q2: BC557; TO-92_Wide
R2: 22k; R_Axial_DIN0204_L3.6mm_D1.6mm_P4mm_Vertical
R6: 180; R_Axial_DIN0204_L3.6mm_D1.6mm_P4mm_Vertical
R7: 100; R_Axial_DIN0204_L3.6mm_D1.6mm_P4mm_Vertical
R10: 1k; R_Axial_DIN0204_L3.6mm_D1.6mm_P4mm_Vertical
U1: 74LS259; DIP-16_W7.62mm
U2: 74LS00; DIP-14_W7.62mm
U3: LM555xN; DIP-8_W7.62mm
U4: 74LS174; DIP-16_W7.62mm
U5: 74LS05; DIP-14_W7.62mm
U7, U11: 74LS138; DIP-16_W7.62mm
U8, U10: N82S135N; DIP-20_W7.62mm
U9: 74LS323; DIP-20_W7.62mm

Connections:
+5V: C1.1, J2.11, J2.12, P1.25, Q2.3 (E), R2.2, R7.2, U1.16 (VCC), U2.14 (VCC), U3.8 (VCC), U4.16 (VCC), U5.14 (VCC), U7.16 (VCC), U8.20 (VCC), U9.20 (VCC), U11.16 (VCC)
+12V: J2.13, J2.15, J2.17, J2.19, P1.50
-12V: J2.9, P1.33
/P2_2M: P1.37, U2.1
/P2_A0: P1.2, U1.13 (D), U9.3 (OE2), U10.1 (A0)
/P2_A1: P1.3, U1.1 (A0), U10.2 (A1)
/P2_A2: P1.4, U1.2 (A1), U10.3 (A2)
/P2_A3: P1.5, U1.3 (A2), U10.4 (A3)
/P2_A4: P1.6, U10.5 (A4), U11.1 (A0)
/P2_A5: P1.7, U10.19 (A7), U11.2 (A1)
/P2_A6: P1.8, U10.18 (A6), U11.3 (A2)
/P2_A7: P1.9, U10.17 (A5), U11.6 (E3)
/P2_A8: P1.10, U7.6 (E3)
/P2_A9: P1.11, U7.1 (A0)
/P2_A10: P1.12, U7.2 (A1)
/P2_A11: P1.13, U7.3 (A2)
/P2_A12: P1.14, U7.5 (E2)
/P2_D0: P1.49, U9.16 (IO7), U10.6 (O1)
/P2_D1: P1.48, U9.4 (IO6), U10.7 (O2)
/P2_D2: P1.47, U9.15 (IO5), U10.8 (O3)
/P2_D3: P1.46, U9.5 (IO4), U10.9 (O4)
/P2_D4: P1.45, U9.14 (IO3), U10.14 (O8)
/P2_D5: P1.44, U9.6 (IO2), U10.13 (O7)
/P2_D6: P1.43, U9.13 (IO1), U10.12 (O6)
/P2_D7: P1.42, U9.7 (IO0), U10.11 (O5)
/P2_EXTC: P1.41, U7.4 (E1)
/P2_EXTM: P1.32, U5.2
/P2_IOSEL: P1.1, U11.5 (E2)
/P2_RESET: P1.31, U1.15 (Clr), U3.4 (R)
/PHIO1: J2.2, U1.4 (Q0)
/PHIO2: J2.4, U1.5 (Q1)
/PHIO3: J2.6, U1.6 (Q2)
/PHIO4: J2.8, U1.7 (Q3)
/RD_DATA: J2.18, U8.19 (A7)
/U1_LATCH5: U1.10 (Q5), U2.5
/U3_OUT: U2.2, U2.4, U2.10, U3.3 (Q), U4.1 (~Mr), U5.11
/U3_OUT2: U5.8, U8.7 (O2), U9.1 (S0)
/U3_TRIGGER: C1.2, R2.1, U3.2 (TR), U3.6 (THR), U5.6
/U4_CLOCK: U2.3, U4.9 (Cp), U9.12 (Cp)
/U8_EN: U5.9, U5.10, U8.15 (~CE2), U8.16 (~CE1)
/U9_PIN8: U8.2 (A1), U9.8 (Q0)
/U10_EN: R6.1, U7.15 (O0), U10.15 (~CE2), U10.16 (~CE1)
/U10_VCC: Q2.1 (C), R10.2, U5.1, U10.20 (VCC)
/U11_PIN14: U1.14 (E), U9.2 (OE1), U11.14 (O1)
/WPROT: J2.20, U9.11 (DS0)
/WR_REQ: J2.10, U5.4
/~ENBL1: J2.14, U2.8
/~U3_TRIGGER: U1.9 (Q4), U5.5
GND: J2.1, J2.3, J2.5, J2.7, P1.26, R10.1, U1.8 (GND), U2.7 (GND), U3.1 (GND), U4.8 (GND), U5.7 (GND), U7.8 (GND), U8.10 (GND), U9.10 (GND), U10.10 (GND), U11.4 (E1), U11.8 (GND)
unnamed: Q2.2 (B), R6.2, R7.1
unnamed: U2.6, U2.9

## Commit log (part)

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2024-08-31 Primeira versão no gitub
2024-08-31 Primeira versão no github
2024-09-02 Finalização da Revisão 1
2024-09-02 Inclusão do conteudo da PAL14L4.
